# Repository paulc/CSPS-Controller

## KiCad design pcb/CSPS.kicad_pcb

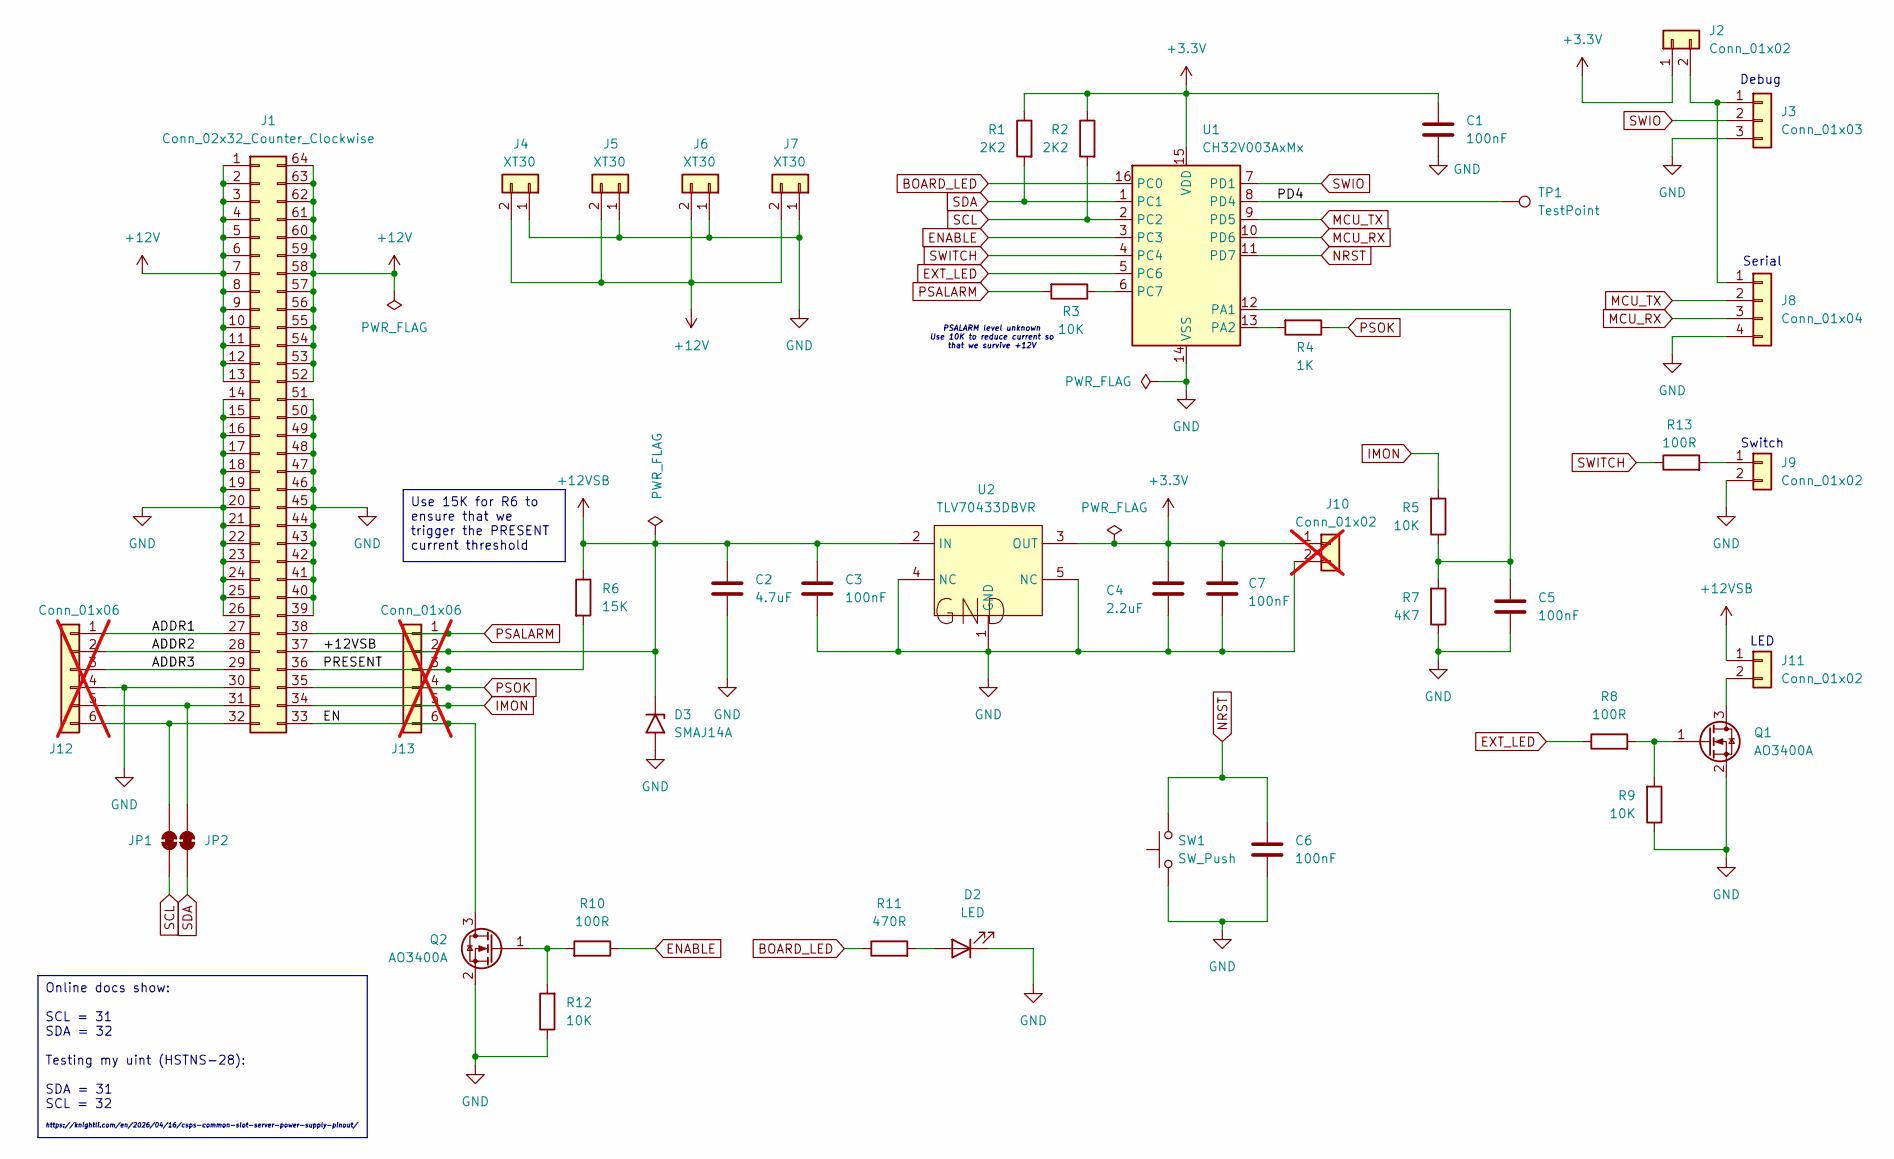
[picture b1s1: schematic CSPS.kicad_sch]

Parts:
C1, C3, C5, C6, C7: 100nF; C_1206_3216Metric_Pad1.33x1.80mm_HandSolder; LCSC C24497
C2: 4.7uF; C_1206_3216Metric_Pad1.33x1.80mm_HandSolder; LCSC C29823
C4: 2.2uF; C_1206_3216Metric_Pad1.33x1.80mm_HandSolder; LCSC C50254
D2: LED; LED_1206_3216Metric_Pad1.42x1.75mm_HandSolder; LCSC C3646937
D3: SMAJ14A; D_SMA; LCSC C908768
J1: Conn_02x32_Counter_Clockwise; 2x32 Edge Connector
J2: Conn_01x02; PinHeader_1x02_P2.54mm_Vertical
J3: Conn_01x03; JST_XH_B3B-XH-A_1x03_P2.50mm_Vertical
J4, J5, J6, J7: XT30; AMASS_XT30U-M_1x02_P5.0mm_Vertical
J8: Conn_01x04; JST_XH_B4B-XH-A_1x04_P2.50mm_Vertical
J9, J11: Conn_01x02; JST_XH_B2B-XH-A_1x02_P2.50mm_Vertical
J10: Conn_01x02; PinHeader_1x02_P2.54mm_Vertical; not fitted
J12, J13: Conn_01x06; PinHeader_1x06_P2.54mm_Vertical; not fitted
JP1, JP2: SolderJumper_2_Bridged; SolderJumper-2_P1.3mm_Bridged_RoundedPad1.0x1.5mm
Q1, Q2: AO3400A; SOT-23; LCSC C347475
R1, R2: 2K2; R_1206_3216Metric_Pad1.30x1.75mm_HandSolder; LCSC C17948
R3, R5, R9, R12: 10K; R_1206_3216Metric_Pad1.30x1.75mm_HandSolder; LCSC C17902
R4: 1K; R_1206_3216Metric_Pad1.30x1.75mm_HandSolder; LCSC C4410
R6: 15K; R_1206_3216Metric_Pad1.30x1.75mm_HandSolder; LCSC C25828
R7: 4K7; R_1206_3216Metric_Pad1.30x1.75mm_HandSolder; LCSC C17936
R8, R10, R13: 100R; R_1206_3216Metric_Pad1.30x1.75mm_HandSolder; LCSC C17901
R11: 470R; R_1206_3216Metric_Pad1.30x1.75mm_HandSolder; LCSC C4502
SW1: SW_Push; 3_4_2 SMD Micro Touch Switch Button; LCSC Part C843659
TP1: TestPoint; TestPoint_THTPad_1.0x1.0mm_Drill0.5mm
U1: CH32V003AxMx; STC_SOP-16_3.9x9.9mm_P1.27mm; LCSC C5346357
U2: TLV70433DBVR; SOT-23-5_L3.0-W1.7-P0.95-LS2.8-BR; MPN TLV70433DBVR; LCSC Part C94917

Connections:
+3.3V: C1.1, C4.1, C7.1, J2.1, J10.1, R1.1, R2.1, U1.15 (VDD), U2.3 (OUT)
+12V: J1.1, J1.2, J1.3, J1.4, J1.5, J1.6, J1.7, J1.8, J1.9, J1.10, J1.11, J1.12, J1.13, J1.52, J1.53, J1.54, J1.55, J1.56, J1.57, J1.58, J1.59, J1.60, J1.61, J1.62, J1.63, J1.64, J4.2, J5.2, J6.2, J7.2
+12VSB: C2.1, C3.1, D3.1 (A1), J1.37, J11.1, J13.2, R6.1, U2.2 (IN)
/ADDR1: J1.27, J12.1
/ADDR2: J1.28, J12.2
/ADDR3: J1.29, J12.3
/EN: J1.33, J13.6, Q2.3 (D)
/PD4: TP1.1 (1_1), U1.8 (PD4)
/PRESENT: J1.36, J13.3, R6.2
BOARD_LED: R11.1, U1.16 (PC0)
ENABLE: R10.1, U1.3 (PC3)
EXT_LED: R8.1, U1.5 (PC6)
GND: C1.2, C2.2, C3.2, C4.2, C5.2, C6.2, C7.2, D2.1 (K), D3.2 (A2), J1.14, J1.15, J1.16, J1.17, J1.18, J1.19, J1.20, J1.21, J1.22, J1.23, J1.24, J1.25, J1.26, J1.30, J1.39, J1.40, J1.41, J1.42, J1.43, J1.44, J1.45, J1.46, J1.47, J1.48, J1.49, J1.50, J1.51, J3.3, J4.1, J5.1, J6.1, J7.1, J8.4, J9.2, J10.2, J12.4, Q1.2 (S), Q2.2 (S), R7.1, R9.1, R12.1, SW1.1, U1.14 (VSS), U2.1 (GND), U2.4 (NC), U2.5 (NC)
IMON: J1.34, J13.5, R5.2
MCU_RX: J8.3, U1.10 (PD6)
MCU_TX: J8.2, U1.9 (PD5)
NRST: C6.1, SW1.2, U1.11 (PD7)
unnamed: D2.2 (A), R11.2
unnamed: J1.31, J12.5, JP2.2 (B)
unnamed: J1.32, J12.6, JP1.2 (B)
unnamed: J2.2, J3.1, J8.1
unnamed: J9.1, R13.2
unnamed: J11.2, Q1.3 (D)
unnamed: Q1.1 (G), R8.2, R9.2
unnamed: Q2.1 (G), R10.2, R12.2
unnamed: C5.1, R5.1, R7.2, U1.12 (PA1)
unnamed: R4.2, U1.13 (PA2)
unnamed: R3.1, U1.6 (PC7)
PSALARM: J1.38, J13.1, R3.2
PSOK: J1.35, J13.4, R4.1
SCL: JP1.1 (A), R2.2, U1.2 (PC2)
SDA: JP2.1 (A), R1.2, U1.1 (PC1)
SWIO: J3.2, U1.7 (PD1)
SWITCH: R13.1, U1.4 (PC4)

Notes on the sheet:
https://knightli.com/en/2026/04/16/csps-common-slot-server-power-supply-pinout/
LED
PSALARM level unknown Use 10K to reduce current so that we survive +12V
Debug
Serial
Switch
Online docs show: SCL = 31 SDA = 32 Testing my uint (HSTNS-28): SDA = 31 SCL = 32
Use 15K for R6 to ensure that we trigger the PRESENT current threshold

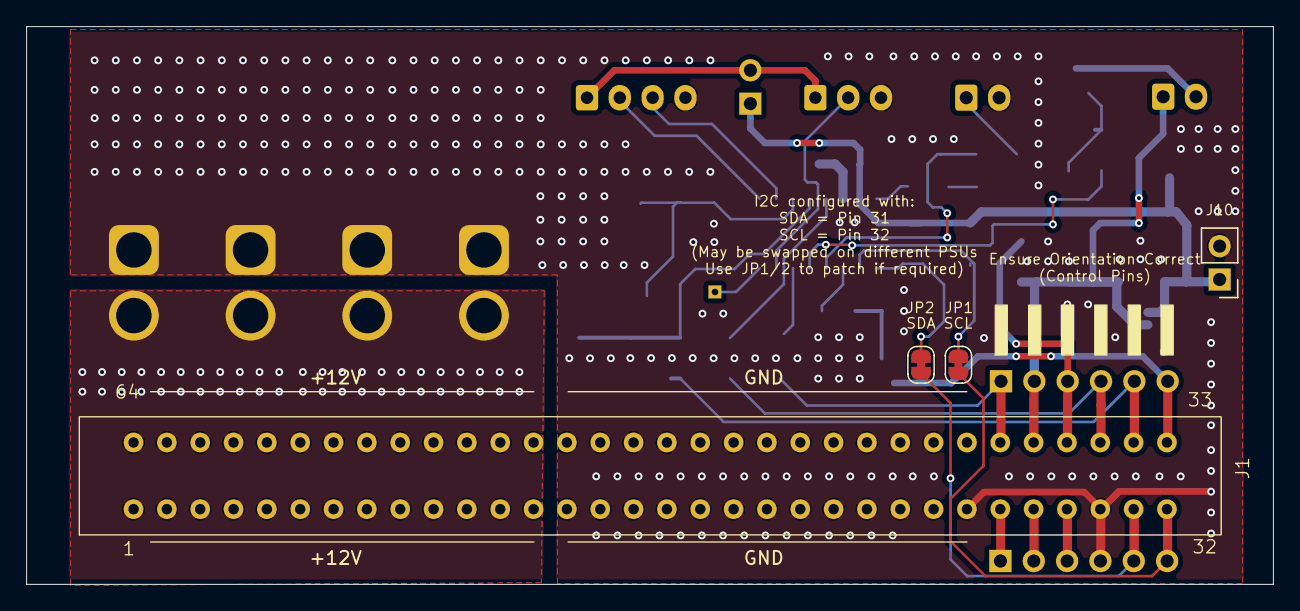
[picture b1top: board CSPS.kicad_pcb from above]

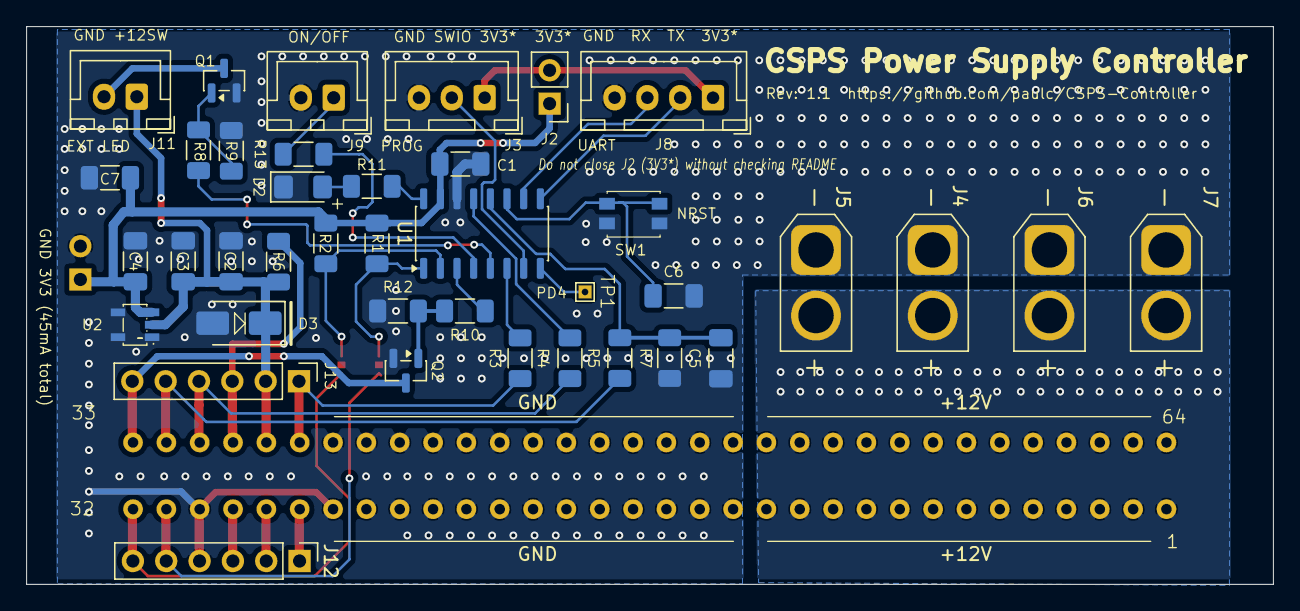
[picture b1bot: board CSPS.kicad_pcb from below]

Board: 2 copper layers, 95.0 x 42.5 mm, 43 parts (39 on the bottom side), 34 nets.

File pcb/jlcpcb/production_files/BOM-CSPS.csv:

Comment,Designator,Footprint,LCSC,Quantity
100R,"R10,R13,R8",R_1206_3216Metric_Pad1.30x1.75mm_HandSolder,C17901,3
100nF,"C1,C3,C5,C6,C7",C_1206_3216Metric_Pad1.33x1.80mm_HandSolder,C24497,5
10K,"R12,R3,R5,R9",R_1206_3216Metric_Pad1.30x1.75mm_HandSolder,C17902,4
15K,R6,R_1206_3216Metric_Pad1.30x1.75mm_HandSolder,C25828,1
1K,R4,R_1206_3216Metric_Pad1.30x1.75mm_HandSolder,C4410,1
2.2uF,C4,C_1206_3216Metric_Pad1.33x1.80mm_HandSolder,C50254,1
2K2,"R1,R2",R_1206_3216Metric_Pad1.30x1.75mm_HandSolder,C17948,2
4.7uF,C2,C_1206_3216Metric_Pad1.33x1.80mm_HandSolder,C29823,1
470R,R11,R_1206_3216Metric_Pad1.30x1.75mm_HandSolder,C4502,1
4K7,R7,R_1206_3216Metric_Pad1.30x1.75mm_HandSolder,C17936,1
AO3400A,"Q1,Q2",SOT-23,C347475,2
CH32V003AxMx,U1,STC_SOP-16_3.9x9.9mm_P1.27mm,C5346357,1
LED,D2,LED_1206_3216Metric_Pad1.42x1.75mm_HandSolder,C3646937,1
SMAJ14A,D3,D_SMA,C908768,1
SW_Push,SW1,3_4_2 SMD Micro Touch Switch Button,C843659,1
TLV70433DBVR,U2,SOT-23-5_L3.0-W1.7-P0.95-LS2.8-BR,C94917,1
Conn_02x32_Counter_Clockwise,J1,2x32 Edge Connector,,1
TestPoint,TP1,TestPoint_THTPad_1.0x1.0mm_Drill0.5mm,,1

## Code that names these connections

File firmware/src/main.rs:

#![no_std]
#![no_main]

use ch32_hal::adc::{Adc, SampleTime, Vref};
use ch32_hal::gpio::{Input, Level, Output, Pull};
use ch32_hal::i2c::I2c;
use ch32_hal::time::Hertz;
use ch32_hal::usart;

use embassy_executor::Spawner;
use embassy_time::{Duration, Instant, Ticker};

use portable_atomic::{AtomicBool, AtomicU16, AtomicU32, AtomicU8, Ordering};

mod iwdg;
mod led_state;
mod line_handler;
mod parse;
mod serial;
mod stack;

use iwdg::{Prescaler, Watchdog};
use led_state::LedState;
use serial::serial_write;

static POWER_STATE: AtomicBool = AtomicBool::new(false);
static LED_STATE: AtomicU8 = AtomicU8::new(0);
static UPTIME: AtomicU32 = AtomicU32::new(0);
static ON_TIMER: AtomicU32 = AtomicU32::new(0);
static OFF_TIMER: AtomicU32 = AtomicU32::new(0);
static POWER_OFF_DELAY: AtomicU32 = AtomicU32::new(5);
static VREF: AtomicU16 = AtomicU16::new(0);
static IMON: AtomicU16 = AtomicU16::new(0);
static PS_OK: AtomicBool = AtomicBool::new(false);
static PS_ALARM: AtomicBool = AtomicBool::new(false);

const WATCHDOG_MS: u32 = 4000;

ch32_hal::bind_interrupts!(struct Irqs {
    USART1 => ch32_hal::usart::InterruptHandler<ch32_hal::peripherals::USART1>;
});

#[embassy_executor::main(entry = "qingke_rt::entry")]
async fn main(spawner: Spawner) -> ! {
    // Paint stack at init
    stack::paint_stack();

    let mut config = ch32_hal::Config::default();
    config.rcc = ch32_hal::rcc::Config::SYSCLK_FREQ_48MHZ_HSI;
    let p = ch32_hal::init(config);

    // Clear reset
    ch32_hal::pac::RCC.rstsckr().modify(|w| w.set_rmvf(true));

    // IO Pins
    let board_led = p.PC0;
    let sda = p.PC1;
    let scl = p.PC2;
    let enable = p.PC3;
    let switch = p.PC4;
    let ext_led = p.PC6;
    let ps_alarm = p.PC7;
    let mcu_tx = p.PD5;
    let mcu_rx = p.PD6;
    let mut imon = p.PA1;
    let ps_ok = p.PA2;

    // Serial
    let uart_config = usart::Config::default(); // 115200,N,8,1
    let (uart_tx, uart_rx) = match usart::Uart::new(
        p.USART1,
        mcu_rx,
        mcu_tx,
        Irqs,
        p.DMA1_CH4,
        p.DMA1_CH5,
        uart_config,
    ) {
        Ok(uart) => uart.split(),
        Err(_) => {
            panic!("uart");
        }
    };

    serial::UCASE.store(true, Ordering::Relaxed);

    // Spawn serial reader/writer tasks
    match serial::serial_read_task(uart_rx) {
        Ok(t) => spawner.spawn(t),
        Err(_) => panic!("serial_read"),
    }
    match serial::serial_write_task(uart_tx) {
        Ok(t) => spawner.spawn(t),
        Err(_) => panic!("serial_write"),
    }

    serial_write(b"-- [[ CH32V003 CSPS ]] --\r\n");
    stack::print_stack();

    // I2C
    let i2c = I2c::new_blocking(p.I2C1, scl, sda, Hertz::hz(100_000), Default::default());

    match line_handler::line_handler(i2c) {
        Ok(t) => spawner.spawn(t),
        Err(_) => panic!("line_handler"),
    }

    // Status task
    let button = Input::new(switch, Pull::Up);
    let mut enable = Output::new(enable, Level::Low, Default::default());
    let mut board_led = Output::new(board_led, Level::Low, Default::default());
    let mut ext_led = Output::new(ext_led, Level::Low, Default::default());
    let ps_alarm = Input::new(ps_alarm, Pull::Down);
    let ps_ok = Input::new(ps_ok, Pull::Down);
    let mut adc = Adc::new(p.ADC1, Default::default());

    // Watchdog
    let mut wdt = match Watchdog::start(Prescaler::Div256, WATCHDOG_MS) {
        Ok(w) => w,
        Err(_) => panic!("watchdog"),
    };

    const STATUS_TICKER_MS: u32 = 50;

    let status_task = async {
        let mut count = 0_u32;
        let mut ticker = Ticker::every(Duration::from_millis(STATUS_TICKER_MS as u64));
        let mut button_ms = 0_u32;
        let mut off_warning = false;

        // Track uptime from ms timer ticks (avoids u64_div_rem)
        let mut last_ms = Instant::now().as_ticks() as u32; // TICK_HZ == 1000
        let mut frac_ms = 0_u32;
        let mut now_s = 0_u32;

        loop {
            // Get uptine in secs
            let ms = Instant::now().as_ticks() as u32;
            frac_ms += ms.wrapping_sub(last_ms);
            last_ms = ms;
            while frac_ms >= 1000 {
                frac_ms -= 1000;
                now_s = now_s.wrapping_add(1);
            }

            // Update status
            UPTIME.store(now_s, Ordering::Relaxed);
            PS_OK.store(ps_ok.is_high(), Ordering::Relaxed);
            PS_ALARM.store(ps_alarm.is_high(), Ordering::Relaxed);
            VREF.store(
                adc.convert(&mut Vref, SampleTime::CYCLES57),
                Ordering::Relaxed,
            );
            IMON.store(
                adc.convert(&mut imon, SampleTime::CYCLES57),
                Ordering::Relaxed,
            );

            // Check for off-warning
            off_warning = if OFF_TIMER.load(Ordering::Relaxed) > 0
                && now_s
                    >= OFF_TIMER.load(Ordering::Relaxed) - POWER_OFF_DELAY.load(Ordering::Relaxed)
            {
                // Only send warning once
                if !off_warning {
                    serial_write(b"!! POWERING DOWN !!\r\n");
                }
                true
            } else {
                false
            };

            // Check button status
            if button.is_low() {
                button_ms = button_ms.saturating_add(STATUS_TICKER_MS);
            } else {
                button_ms = 0;
            }

            // Check for short/long press
            match button_ms {
                100..=500 => {
                    // Short Press
                    if !POWER_STATE.load(Ordering::Relaxed) {
                        ON_TIMER.store(now_s, Ordering::Relaxed);
                    }
                    // If off-warning is active cancel
                    if off_warning {
                        OFF_TIMER.store(0, Ordering::Relaxed);
                    }
                }
                2000..=5000 => {
                    // Long Press
                    if POWER_STATE.load(Ordering::Relaxed) {
                        OFF_TIMER.store(
                            now_s + POWER_OFF_DELAY.load(Ordering::Relaxed),
                            Ordering::Relaxed,
                        );
                    }
                }
                _ => {}
            }

            // Check power on timer
            if ON_TIMER.load(Ordering::Relaxed) > 0 && now_s >= ON_TIMER.load(Ordering::Relaxed) {
                enable.set_high();
                POWER_STATE.store(true, Ordering::Relaxed);
                serial_write(b"!! POWER ON !!\r\n");
                ON_TIMER.store(0, Ordering::Relaxed);
            }

            // Check power off timer
            if OFF_TIMER.load(Ordering::Relaxed) > 0 && now_s >= OFF_TIMER.load(Ordering::Relaxed) {
                enable.set_low();
                POWER_STATE.store(false, Ordering::Relaxed);
                serial_write(b"!! POWER OFF !!\r\n");
                OFF_TIMER.store(0, Ordering::Relaxed);
            }

            // Update LED state
            if button_ms >= 500 && button_ms <= 2000 {
                LED_STATE.store(LedState::FastFlash as u8, Ordering::Relaxed);
            } else {
                LED_STATE.store(
                    if off_warning {
                        LedState::SlowFlash as u8
                    } else if POWER_STATE.load(Ordering::Relaxed) {
                        LedState::On as u8
                    } else {
                        LedState::Off as u8
                    },
                    Ordering::Relaxed,
                )
            }

            // Update LED
            for led in [&mut board_led, &mut ext_led] {
                match LedState::from(LED_STATE.load(Ordering::Relaxed)) {
                    LedState::Off => led.set_low(),
                    LedState::On => led.set_high(),
                    LedState::SlowFlash => {
                        if count.is_multiple_of(8) {
                            led.toggle()
                        }
                    }
                    LedState::FastFlash => {
                        if count.is_multiple_of(2) {
                            led.toggle()
                        }
                    }
                    _ => {}
                }
            }

            count = count.wrapping_add(1);
            wdt.feed();
            ticker.next().await;
        }
    };

    // let _ = join(status_task, button_task::button_task(button, enable)).await;

    status_task.await;

    loop {
        let _ = core::future::pending::<()>().await;
    }
}

#[panic_handler]
fn panic(_info: &core::panic::PanicInfo) -> ! {
    loop {}
}
